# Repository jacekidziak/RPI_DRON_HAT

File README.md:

# RPI_DRON_HAT
Project of PCB with servo driver, battery voltage measurement, IMU, GPS and barometr

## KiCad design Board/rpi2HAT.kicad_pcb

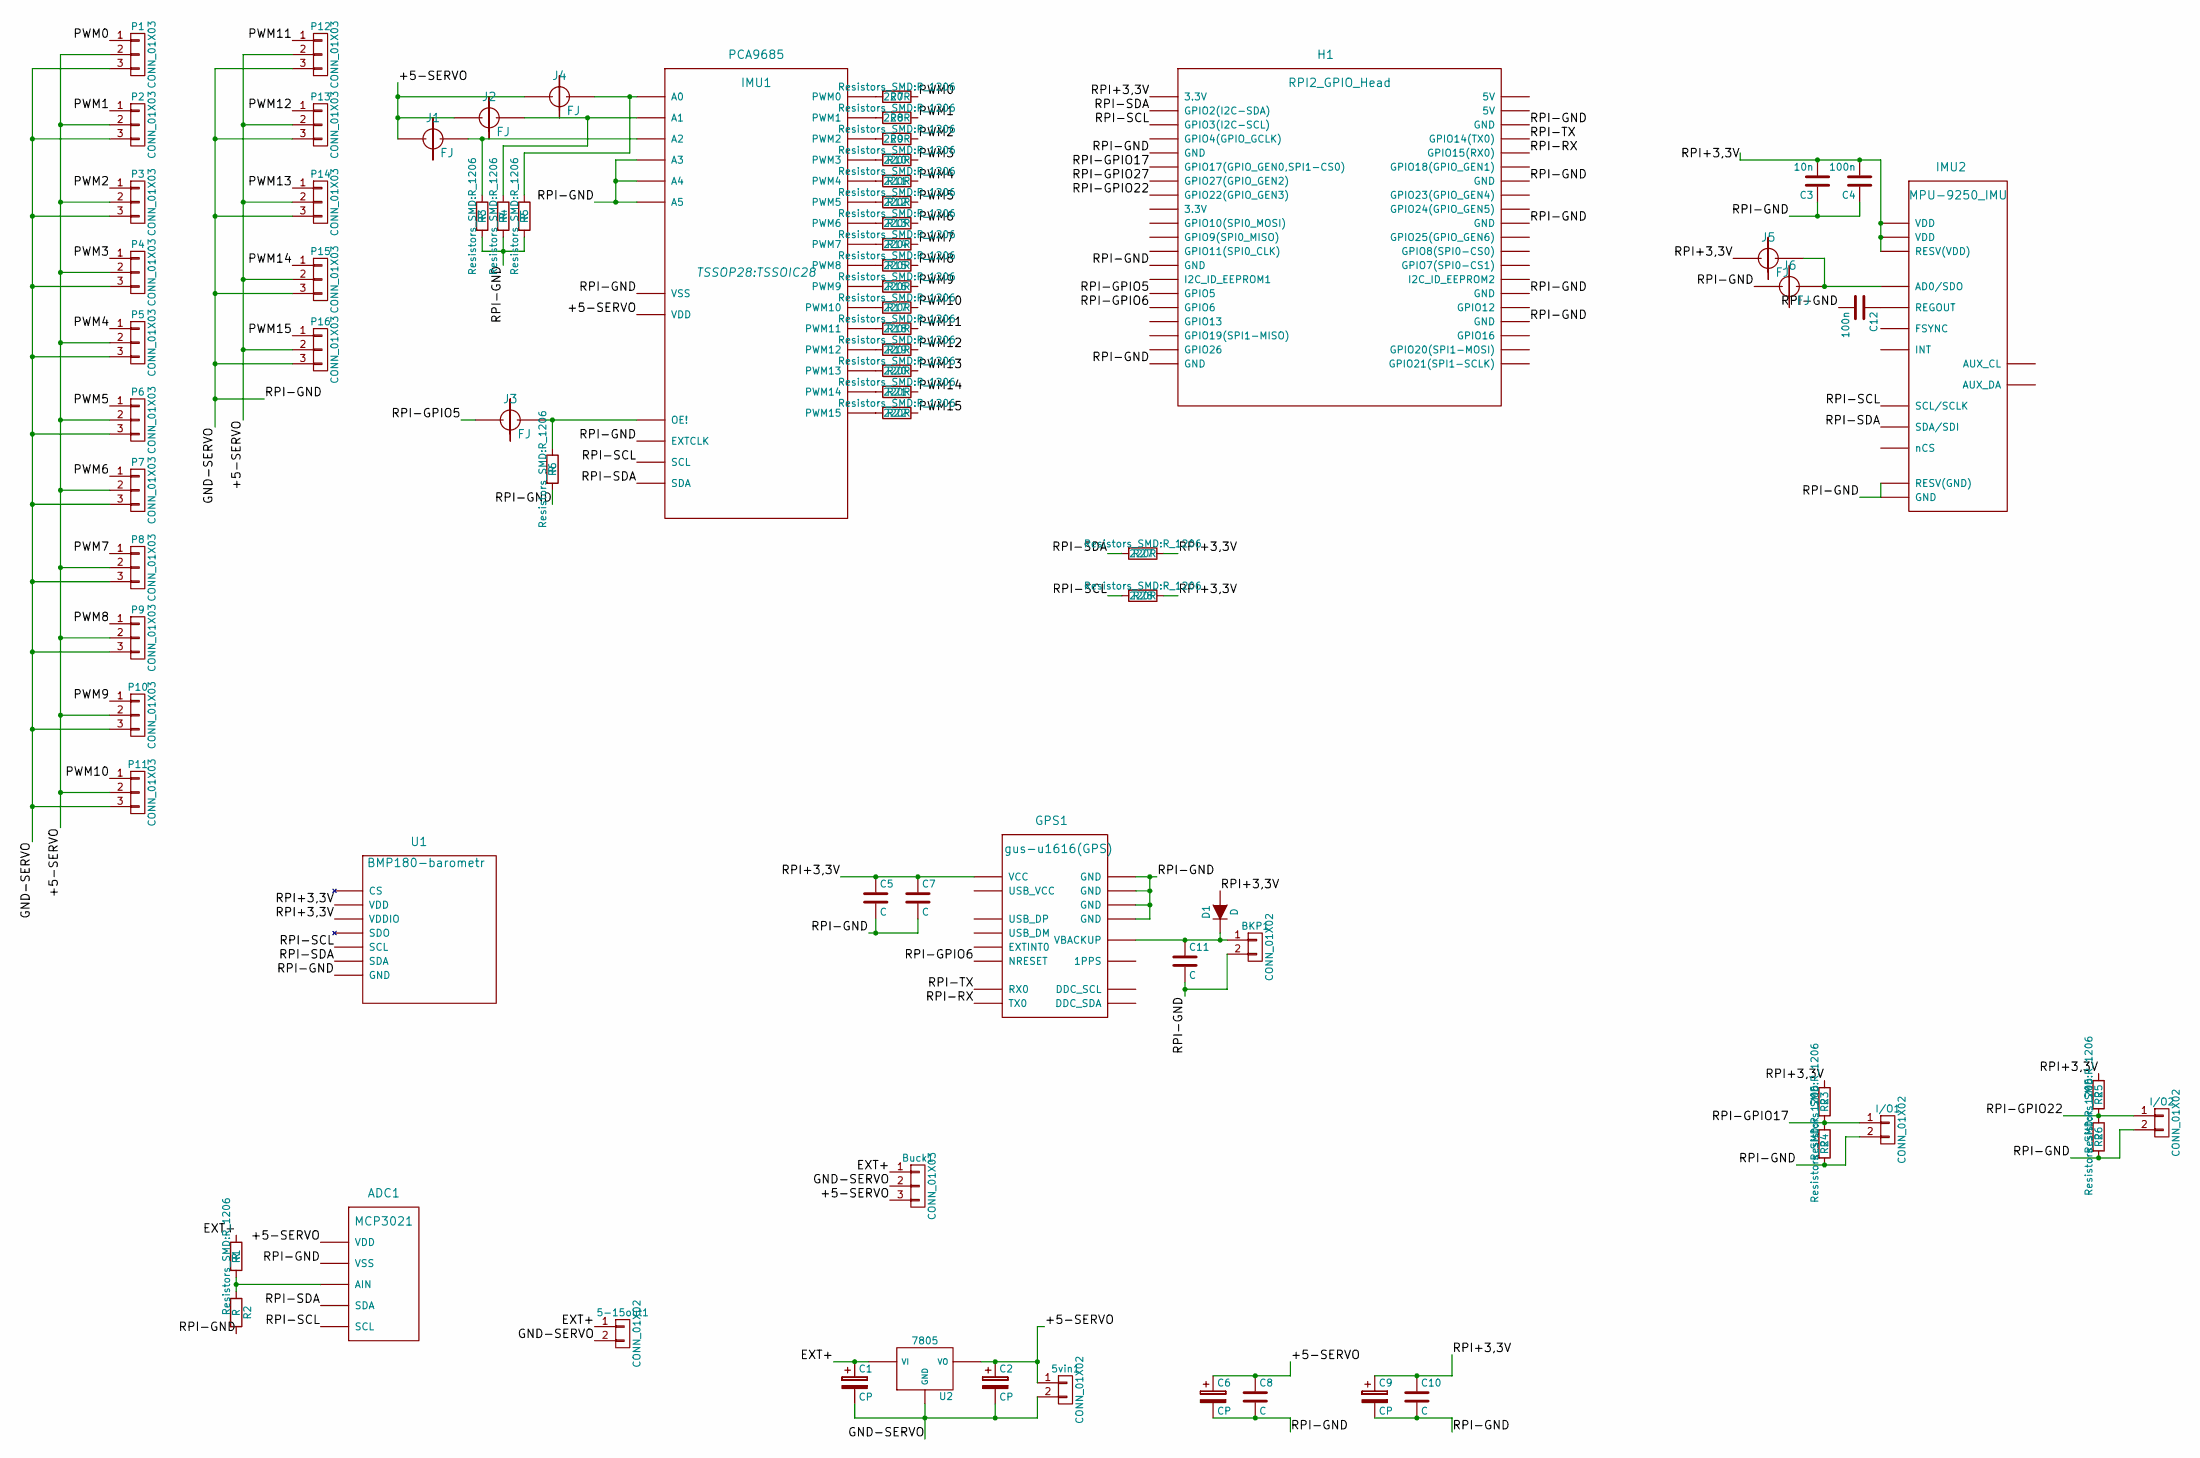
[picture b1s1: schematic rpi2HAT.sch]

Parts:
5-15out1, 5vin1: CONN_01X02; Pin_Header_Straight_1x02
ADC1: MCP3021; SOT23A
BKP1: CONN_01X02; Pin_Header_Straight_1x02
Buck1: CONN_01X03; Pin_Header_Straight_1x03
C1, C2: CP; C_Radial_D6.3_L11.2_P2.5
C3: 10n; C_0603_HandSoldering
C4: 100n; C_0603_HandSoldering
C5, C7, C8, C10, C11: C; C_1206
C6, C9: CP; C_1206
C12: 100n; C_1206
D1: D; SOD-123
GPS1: gus-u1616(GPS); GUS-custimezed
H1: RPI2_GPIO_Head; RPI2-HEAD
I/O1, I/O2: CONN_01X02; Pin_Header_Straight_1x02
IMU1: PCA9685; TSSOIC28
IMU2: MPU-9250_IMU; 3X3X1QFN
J1, J2, J3, J4, J5, J6: FJ; FIXED_JUMPER
P1, P2, P3, P4, P5, P6, P7, P8, P9, P10, P11, P12, P13, P14, P15, P16: CONN_01X03; Pin_Header_Straight_1x03
R1, R2, R3, R4, R5, R6, R23, R24, R25, R26: R; R_1206
R7, R8, R9, R10, R11, R12, R13, R14, R15, R16, R17, R18, R19, R20, R21, R22, R27, R28: 220R; R_1206
U1: BMP180-barometr; BMP180
U2: 7805; DPAK

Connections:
/+5-SERVO: 5vin1.1, ADC1.1 (VDD), Buck1.3, C2.1, C6.1, C8.1, IMU1.28 (VDD), J1.1, J2.1, J4.1, P1.2, P2.2, P3.2, P4.2, P5.2, P6.2, P7.2, P8.2, P9.2, P10.2, P11.2, P12.2, P13.2, P14.2, P15.2, P16.2, U2.VO
/EXT+: 5-15out1.1, Buck1.1, C1.1, R1.1, U2.VI
/GND-SERVO: 5-15out1.2, 5vin1.2, ADC1.2 (VSS), BKP1.2, Buck1.2, C1.2, C2.2, C3.1, C4.1, C5.2, C6.2, C7.2, C8.2, C9.2, C10.2, C11.2, C12.2, GPS1.3 (GND), GPS1.8 (GND), GPS1.12 (GND), GPS1.19 (GND), H1.6 (GND), H1.9 (GND), H1.14 (GND), H1.20 (GND), H1.25 (GND), H1.30 (GND), H1.34 (GND), H1.39 (GND), I/O1.2, I/O2.2, IMU1.4 (A3), IMU1.5 (A4), IMU1.14 (VSS), IMU1.24 (A5), IMU1.25 (EXTCLK), IMU2.18 (GND), IMU2.20 (RESV(GND)), J6.1, P1.3, P2.3, P3.3, P4.3, P5.3, P6.3, P7.3, P8.3, P9.3, P10.3, P11.3, P12.3, P13.3, P14.3, P15.3, P16.3, R2.2, R3.2, R4.2, R5.2, R6.2, R24.2, R26.2, U1.7 (GND), U2.GND
/PWM0: P1.1, R7.1
/PWM1: P2.1, R8.1
/PWM2: P3.1, R9.1
/PWM3: P4.1, R10.1
/PWM4: P5.1, R11.1
/PWM5: P6.1, R12.1
/PWM6: P7.1, R13.1
/PWM7: P8.1, R14.1
/PWM8: P9.1, R15.1
/PWM9: P10.1, R16.1
/PWM10: P11.1, R17.1
/PWM11: P12.1, R18.1
/PWM12: P13.1, R19.1
/PWM13: P14.1, R20.1
/PWM14: P15.1, R21.1
/PWM15: P16.1, R22.1
/RPI+3,3V: C3.2, C4.2, C5.1, C7.1, C9.1, C10.1, D1.2 (A), GPS1.1 (VCC), H1.1 (3.3V), IMU2.1 (RESV(VDD)), IMU2.8 (VDD), IMU2.13 (VDD), J5.1, R23.1, R25.1, R27.1, R28.1, U1.2 (VDD), U1.3 (VDDIO)
/RPI-GPIO5: H1.29 (GPIO5), J3.1
/RPI-GPIO6: GPS1.7 (NRESET), H1.31 (GPIO6)
/RPI-GPIO17: H1.11 (GPIO17(GPIO_GEN0,SPI1-CS0)), I/O1.1, R23.2, R24.1
/RPI-GPIO22: H1.15 (GPIO22(GPIO_GEN3)), I/O2.1, R25.2, R26.1
/RPI-RX: GPS1.10 (TX0), H1.10 (GPIO15(RX0))
/RPI-SCL: ADC1.5 (SCL), H1.5 (GPIO3(I2C-SCL)), IMU1.26 (SCL), IMU2.23 (SCL/SCLK), R28.2, U1.5 (SCL)
/RPI-SDA: ADC1.4 (SDA), H1.3 (GPIO2(I2C-SDA)), IMU1.27 (SDA), IMU2.24 (SDA/SDI), R27.2, U1.6 (SDA)
/RPI-TX: GPS1.9 (RX0), H1.8 (GPIO14(TX0))
unnamed: ADC1.3 (AIN), R1.2, R2.1
unnamed: BKP1.1, C11.1, D1.1 (K), GPS1.20 (VBACKUP)
unnamed: C12.1, IMU2.10 (REGOUT)
unnamed: IMU1.1 (A0), J4.2, R5.1
unnamed: IMU1.2 (A1), J2.2, R4.1
unnamed: IMU1.3 (A2), J1.2, R3.1
unnamed: IMU1.6 (PWM0), R7.2
unnamed: IMU1.7 (PWM1), R8.2
unnamed: IMU1.8 (PWM2), R9.2
unnamed: IMU1.9 (PWM3), R10.2
unnamed: IMU1.10 (PWM4), R11.2
unnamed: IMU1.11 (PWM5), R12.2
unnamed: IMU1.12 (PWM6), R13.2
unnamed: IMU1.13 (PWM7), R14.2
unnamed: IMU1.15 (PWM8), R15.2
unnamed: IMU1.16 (PWM9), R16.2
unnamed: IMU1.17 (PWM10), R17.2
unnamed: IMU1.18 (PWM11), R18.2
unnamed: IMU1.19 (PWM12), R19.2
unnamed: IMU1.20 (PWM13), R20.2
unnamed: IMU1.21 (PWM14), R21.2
unnamed: IMU1.22 (PWM15), R22.2
unnamed: IMU1.23 (OE!), J3.2, R6.1
unnamed: IMU2.9 (AD0/SDO), J5.2, J6.2

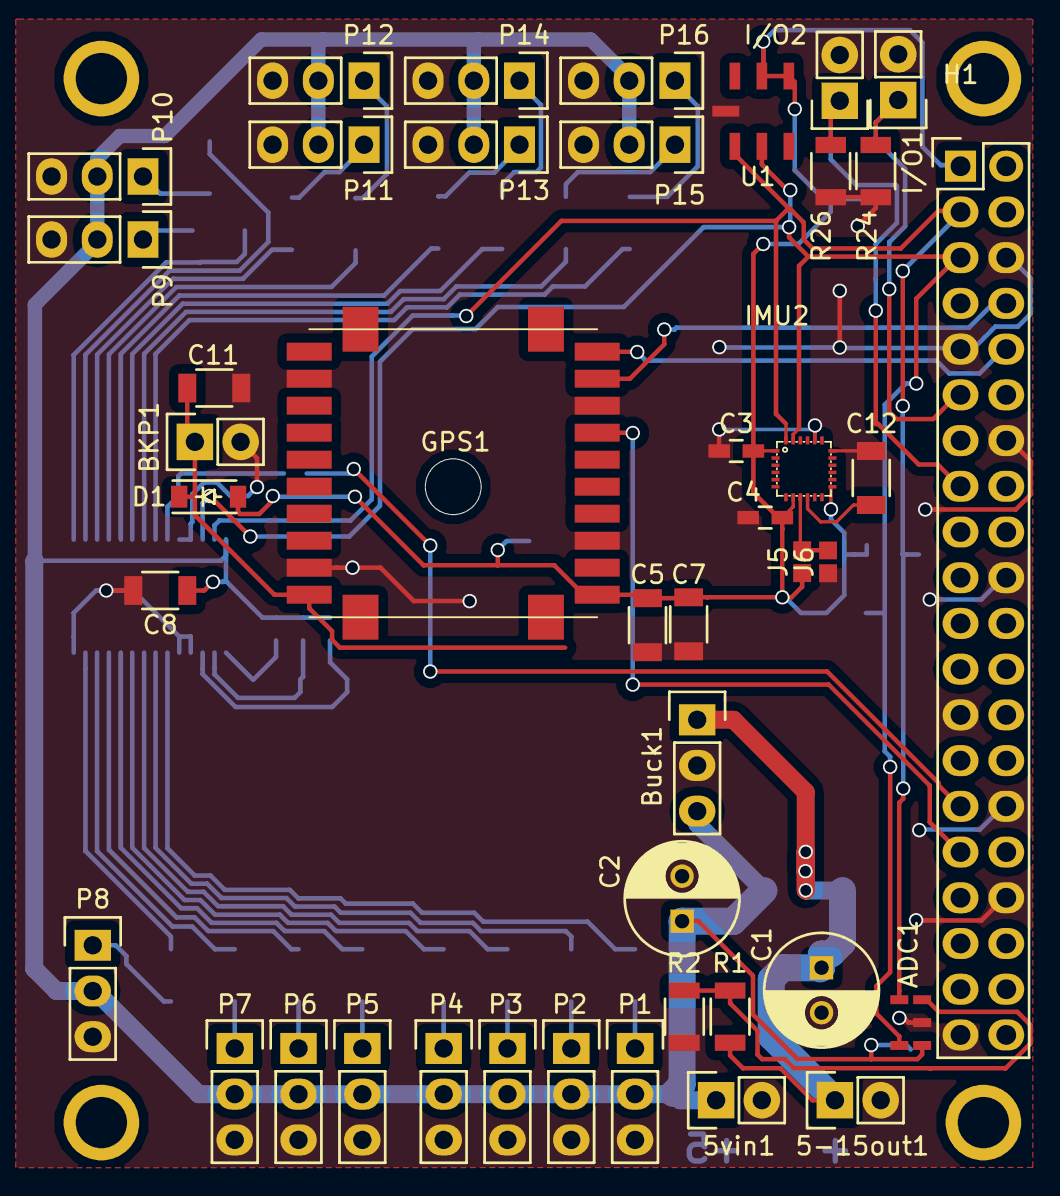
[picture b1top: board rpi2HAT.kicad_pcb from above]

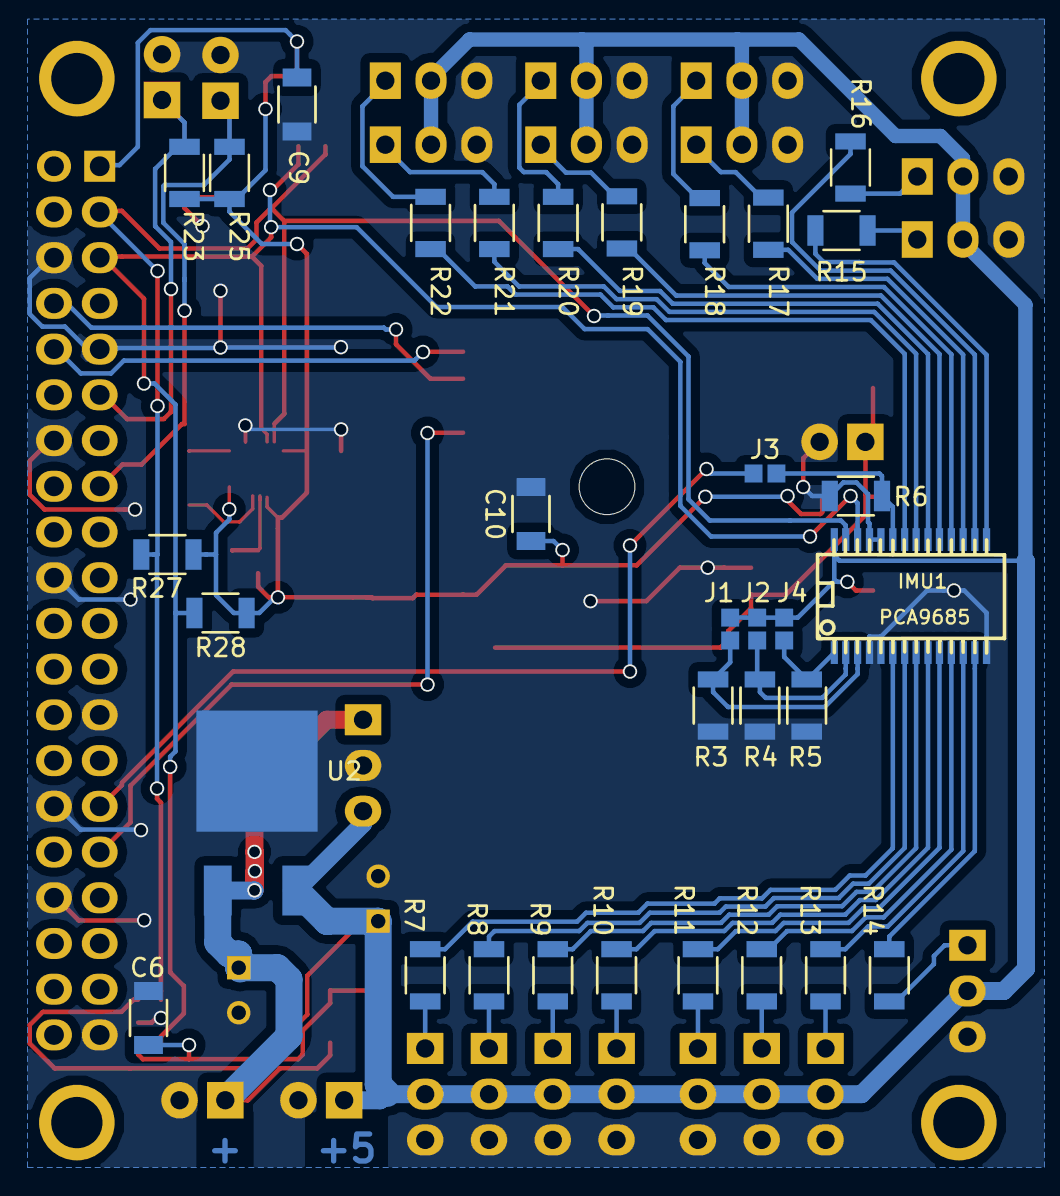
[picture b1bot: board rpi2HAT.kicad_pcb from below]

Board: 2 copper layers, 76 parts (33 on the bottom side), 52 nets.

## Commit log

2016-03-01 Initial revision. PCB RPI2 size. Linear 7805 voltage stabilizer. Initial version. Linear stablizier
2016-03-01 Changed barometr to BMP280. Still Uncut version for rpi2.
2016-03-01 Corrected some footprints.
2016-03-05 Nowa wersja - rpi zero +, tylko 2 warstwy!
2016-03-05 Bazeline documents: rpi2HAT.sch rpiHATv2.net zero+.kicad.pcb
2016-03-11 Added zones for buc/boost converter. changed pad filling
2016-03-11 corrected clereance in zones, fixed some grounding issues
2016-03-11 Minor placement addjustment.
2016-04-22 Final version, gerber went to production.
2016-04-22 added all components values on sch.
2019-03-11 zdjecia
